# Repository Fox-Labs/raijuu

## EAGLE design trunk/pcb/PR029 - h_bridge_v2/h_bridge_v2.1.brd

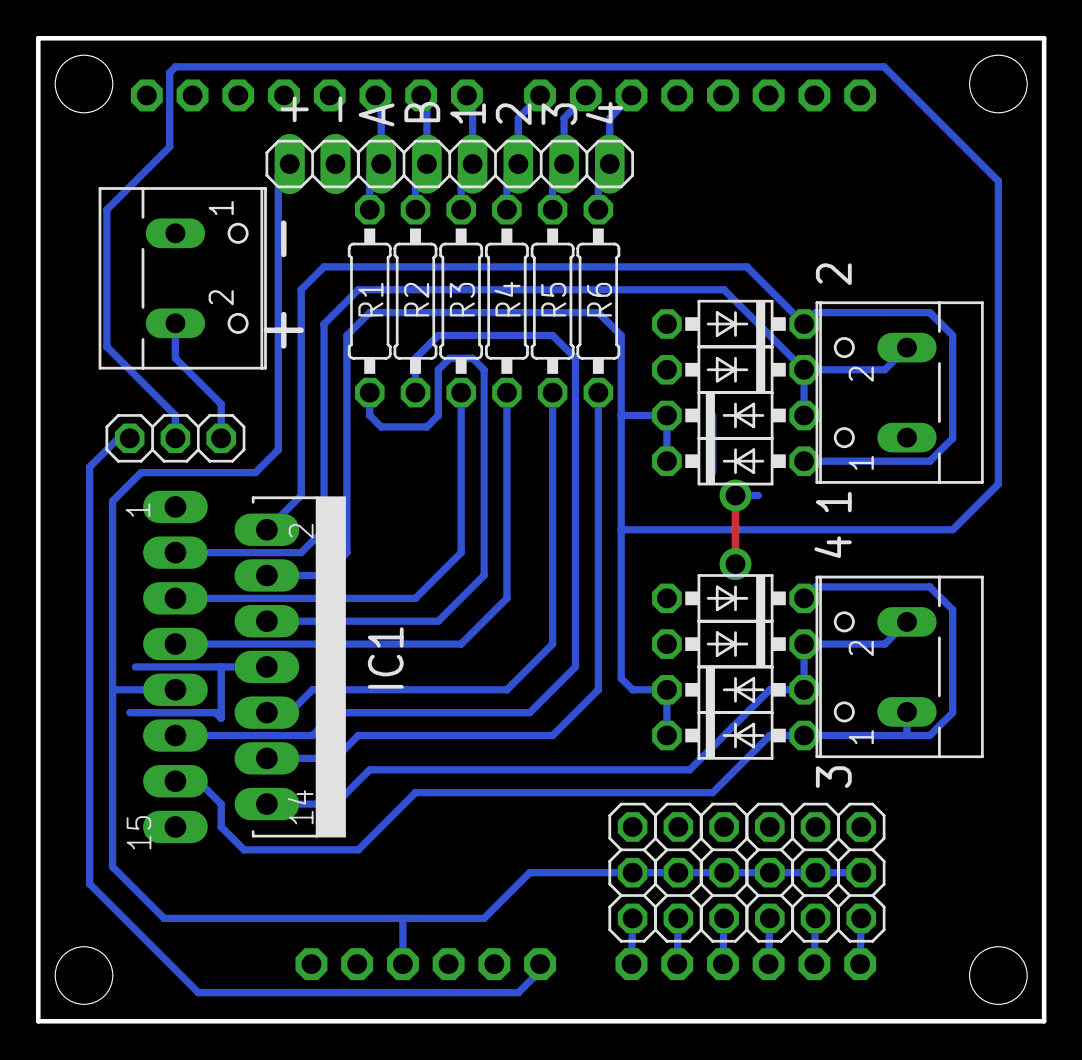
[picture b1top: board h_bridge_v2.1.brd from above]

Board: 2 copper layers, 55.9 x 54.6 mm, 28 parts (0 on the bottom side), 27 nets.

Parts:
D1, D2, D3, D4, D5, D6, D7, D8: 1N4004A; DO41-10
IC1: L298; MULTIWATT-15
JP1: 1X06
JP2, JP3, JP4, JP5, JP6, JP7, JP8: 1X03
JP9: 1X02
R1, R2, R3, R4, R5, R6: 0207/10
U$1: ARDUINO-HOLE
X1, X2, X3: W237-102

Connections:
+5V: IC1.9, JP3.2, JP4.2, JP5.2, JP6.2, JP7.2, JP8.2, JP9.1, U$1.5V
+12V: D1.C, D2.C, D5.C, D6.C, IC1.4, JP2.2
GND: D3.A, D4.A, D7.A, D8.A, IC1.1, IC1.8, IC1.15, JP3.3, JP4.3, JP5.3, JP6.3, JP7.3, JP8.3, JP9.2, U$1.GND, U$1.GND1, U$1.GND2, X3.1
IN_A1: JP1.3, R3.1, U$1.D8
IN_A2: JP1.4, R4.1, U$1.D7
IN_B1: JP1.5, R5.1, U$1.D6
IN_B2: JP1.6, R6.1, U$1.D5
unnamed: IC1.6, R1.2
unnamed: IC1.11, R2.2
unnamed: IC1.5, R3.2
unnamed: IC1.7, R4.2
unnamed: IC1.10, R5.2
unnamed: IC1.12, R6.2
unnamed: JP3.1, U$1.A0
unnamed: JP4.1, U$1.A1
unnamed: JP5.1, U$1.A2
unnamed: JP6.1, U$1.A3
unnamed: JP7.1, U$1.A4
unnamed: JP8.1, U$1.A5
OUT1: D2.A, D4.C, IC1.2, X1.1
OUT2: D1.A, D3.C, IC1.3, X1.2
OUT3: D6.A, D8.C, IC1.13, X2.1
OUT4: D5.A, D7.C, IC1.14, X2.2
PWM_A: JP1.1, R1.1, U$1.D10
PWM_B: JP1.2, R2.1, U$1.D9
PWR: JP2.3, X3.2
VIN: JP2.1, U$1.VIN

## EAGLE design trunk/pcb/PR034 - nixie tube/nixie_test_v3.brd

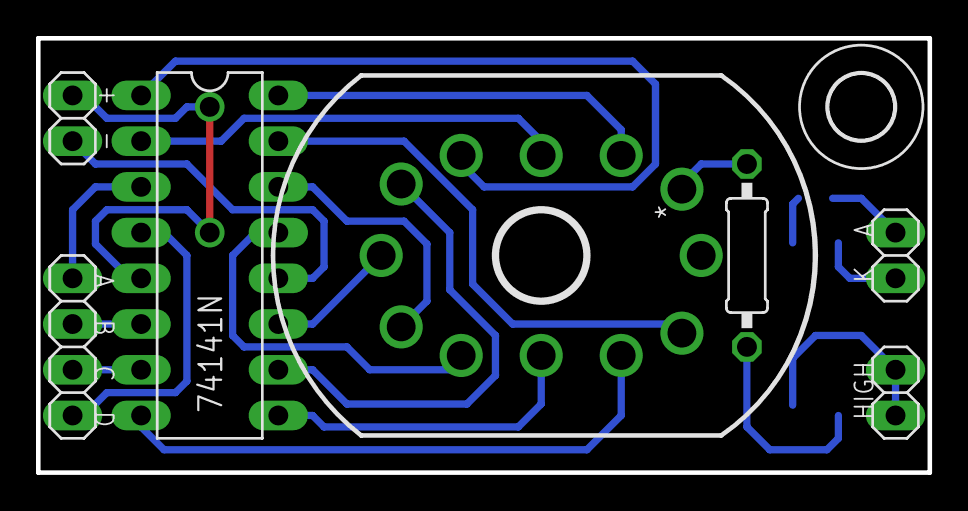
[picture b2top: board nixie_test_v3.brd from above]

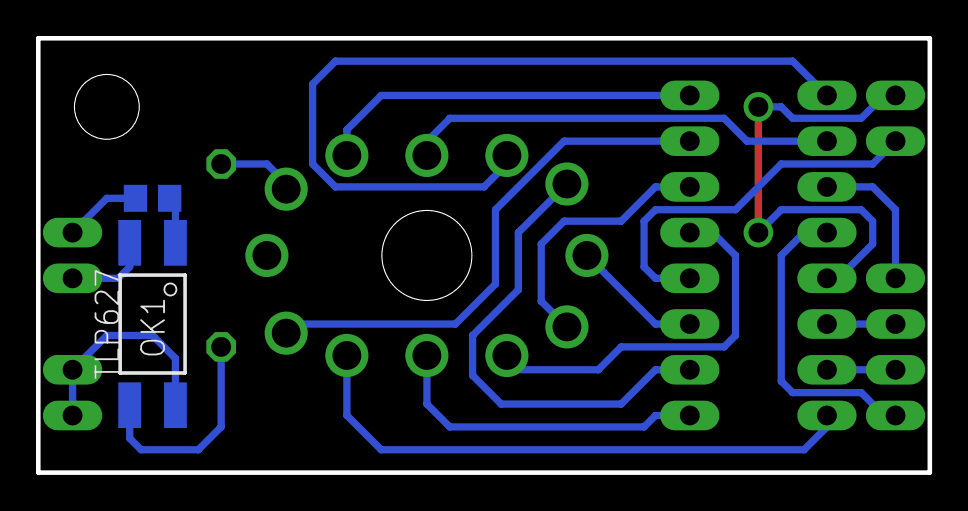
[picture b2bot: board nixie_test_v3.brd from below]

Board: 2 copper layers, 49.5 x 24.1 mm, 10 parts (2 on the bottom side), 22 nets.

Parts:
IC1: 74141N; DIL16
JP1: 1X04
JP2, JP3, JP4: 1X02
N1: IN-12B; IN-12
OK1: TLP627; 4-SMD
R1: 1k; R0805
R2: 22k; 0207/10
U$1: 3,6

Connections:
+5V: IC1.5, JP4.1
+180V: JP3.1, JP3.2, OK1.4
A: IC1.3, JP1.1
B: IC1.6, JP1.2
C: IC1.7, JP1.3
C0: IC1.16, N1.0
C1: IC1.15, N1.1
C2: IC1.8, N1.2
C3: IC1.9, N1.3
C4: IC1.13, N1.4
C5: IC1.14, N1.5
C6: IC1.11, N1.6
C7: IC1.10, N1.7
C8: IC1.1, N1.8
C9: IC1.2, N1.9
D: IC1.4, JP1.4
GND: IC1.12, JP4.2
LA: JP2.1, R1.1
LK: JP2.2, OK1.2
unnamed: N1.A, R2.1
unnamed: OK1.3, R2.2
unnamed: OK1.1, R1.2

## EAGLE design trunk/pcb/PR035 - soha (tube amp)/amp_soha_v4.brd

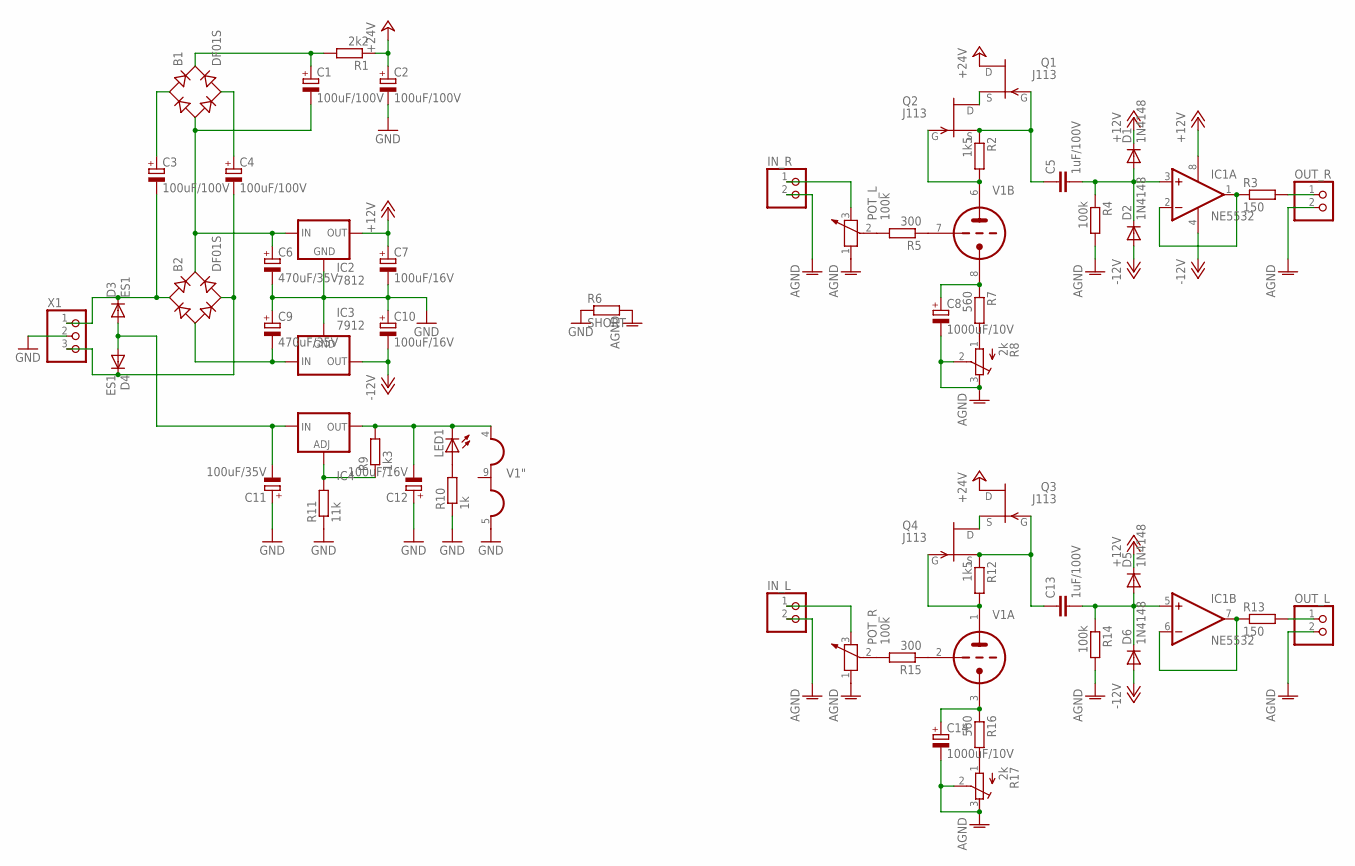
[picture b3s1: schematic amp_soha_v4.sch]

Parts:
B1, B2: DF01S; DFS
C1, C2, C3, C4: 100uF/100V; E5-10,5
C5, C13: 1uF/100V; C075-052X106
C6, C9: 470uF/35V; E5-10,5
C7, C10, C12: 100uF/16V; E2,5-6
C8, C14: 1000uF/10V; E5-10,5
C11: 100uF/35V; E2,5-6
D1, D2, D5, D6: 1N4148; D0805
D3, D4: ES1; DO-214AC
IC1: NE5532; SO08
IC2: 7812; 78XXS
IC3: 7912; 79XXS
IC4: LM337TS; 337TS
IN_L: PINHD-1X2; 1X02
IN_R: PINHD-1X2; 1X02
LED1: LED5MM
OUT_L: PINHD-1X2; 1X02
OUT_R: PINHD-1X2; 1X02
POT_L: 100k; 1X03
POT_R: 100k; 1X03
Q1, Q2, Q3, Q4: J113; TO92
R1: 2k2; R0805
R2, R12: 1k5; R0805
R3, R13: 150; R0805
R4, R14: 100k; R0805
R5, R15: 300; R0805
R6: SHORT
R7, R16: 560; R0805
R8, R17: 2k; RTRIM3296W
R9: 1k3; R0805
R10: 1k; R0805
R11: 11k; R0805
V1: 12AU7-P; NOVAL
X1: W237-103

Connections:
+12V: C7.+, D1.K (C), D5.K (C), IC1.8 (V+), IC2.OUT
+24V: C2.+, Q1.3 (D), Q3.3 (D), R1.1
-12.6V: C12.-, IC4.3 (OUT), LED1.K (C), R9.2, V1.4 (H1)
-12V: C10.-, D2.A, D6.A, IC1.4 (V-), IC3.OUT
AGND: C8.-, C14.-, IN_L.2, IN_R.2, OUT_L.2, OUT_R.2, POT_L.1, POT_R.1, R4.2, R6.2, R8.2 (S), R8.3 (E), R14.2, R17.2 (S), R17.3 (E)
GND: C2.-, C6.-, C7.-, C9.+, C10.+, C11.+, C12.+, IC2.GND, IC3.GND, R6.1, R10.1, R11.1, V1.5 (H3), X1.2
unnamed: B2.AC1, C3.-, D3.C, X1.1
unnamed: B2.AC2, C4.-, D4.C, X1.3
unnamed: C11.-, D3.A, D4.A, IC4.2 (IN)
unnamed: IC4.1 (ADJ), R9.1, R11.2
unnamed: B2.-, C9.-, IC3.IN
unnamed: B1.-, B2.+, C1.-, C6.+, IC2.IN
unnamed: LED1.A, R10.2
unnamed: B1.AC1, C3.+
unnamed: B1.AC2, C4.+
unnamed: R15.1, V1.2 (TG)
unnamed: B1.+, C1.+, R1.2
unnamed: IN_R.1, POT_L.3 (2)
unnamed: POT_L.2 (3), R5.2
unnamed: R5.1, V1.7 (TG)
unnamed: C8.+, R7.1, V1.8 (TK)
unnamed: C5.1, Q1.1 (G), Q2.2 (S), R2.1
unnamed: R7.2, R8.1 (A)
unnamed: R16.2, R17.1 (A)
unnamed: Q2.1 (G), R2.2, V1.6 (TA)
unnamed: Q1.2 (S), Q2.3 (D)
unnamed: Q4.1 (G), R12.2, V1.1 (TA)
unnamed: C5.2, D1.A, D2.K (C), IC1.3 (+IN), R4.1
unnamed: IC1.1 (OUT), IC1.2 (-IN), R3.1
unnamed: OUT_R.1, R3.2
unnamed: IN_L.1, POT_R.3 (2)
unnamed: POT_R.2 (3), R15.2
unnamed: C14.+, R16.1, V1.3 (TK)
unnamed: C13.1, Q3.1 (G), Q4.2 (S), R12.1
unnamed: Q3.2 (S), Q4.3 (D)
unnamed: C13.2, D5.A, D6.K (C), IC1.5 (+IN), R14.1
unnamed: IC1.6 (-IN), IC1.7 (OUT), R13.1
unnamed: OUT_L.1, R13.2

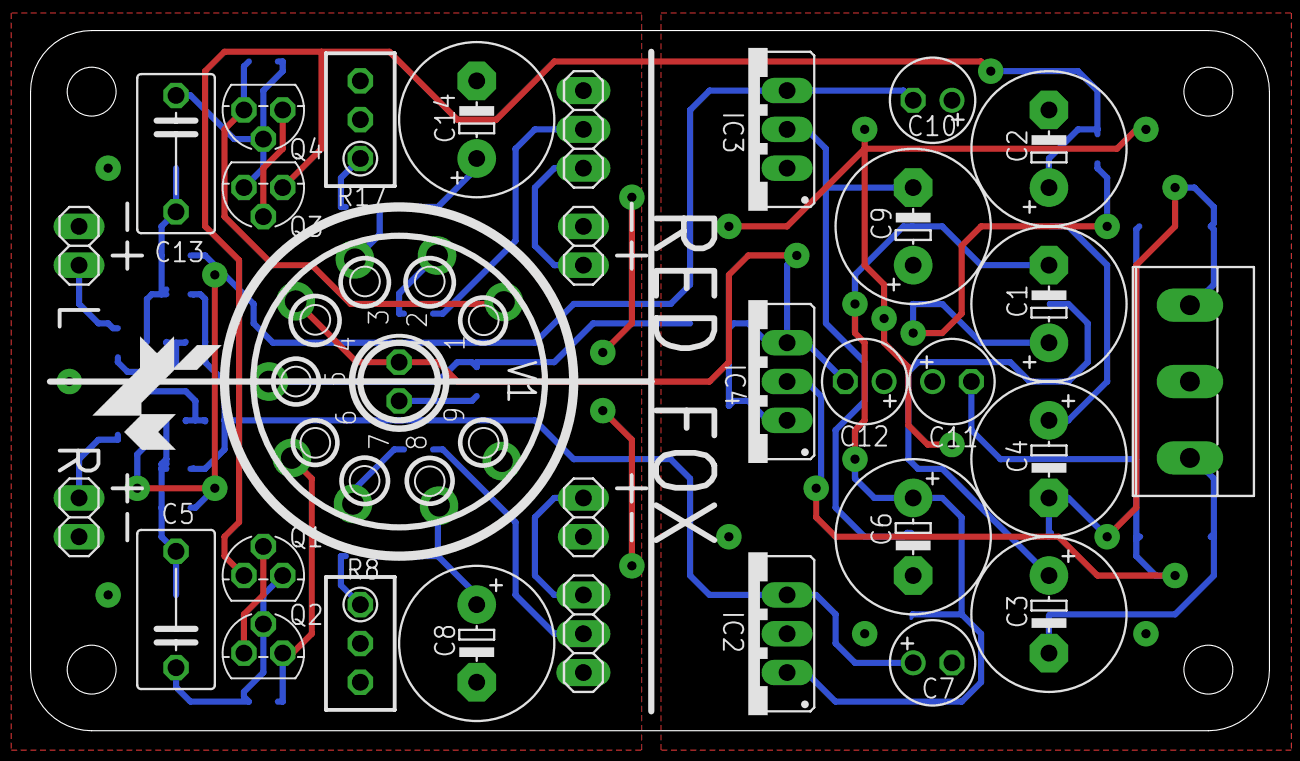
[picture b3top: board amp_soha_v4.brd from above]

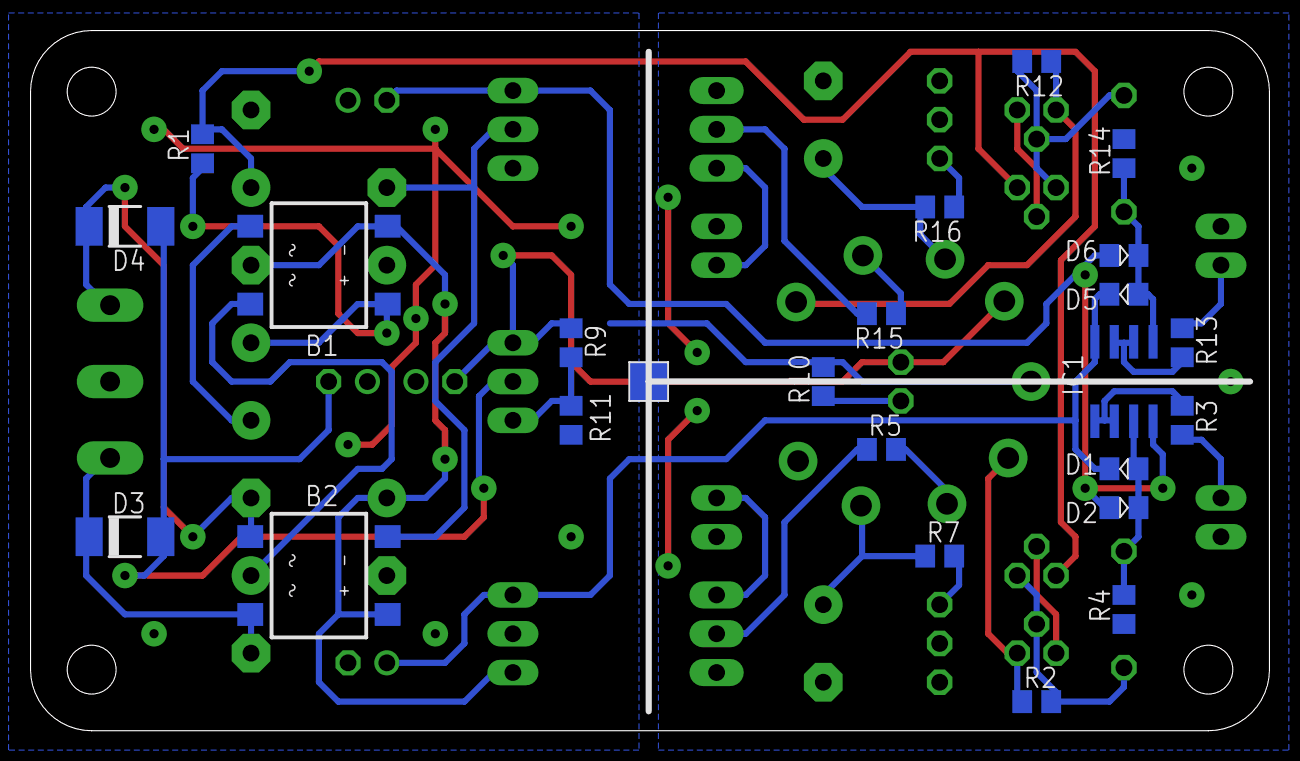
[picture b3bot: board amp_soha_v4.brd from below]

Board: 2 copper layers, 81.1 x 45.8 mm, 57 parts (24 on the bottom side), 38 nets.

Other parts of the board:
U$1: FOX-2

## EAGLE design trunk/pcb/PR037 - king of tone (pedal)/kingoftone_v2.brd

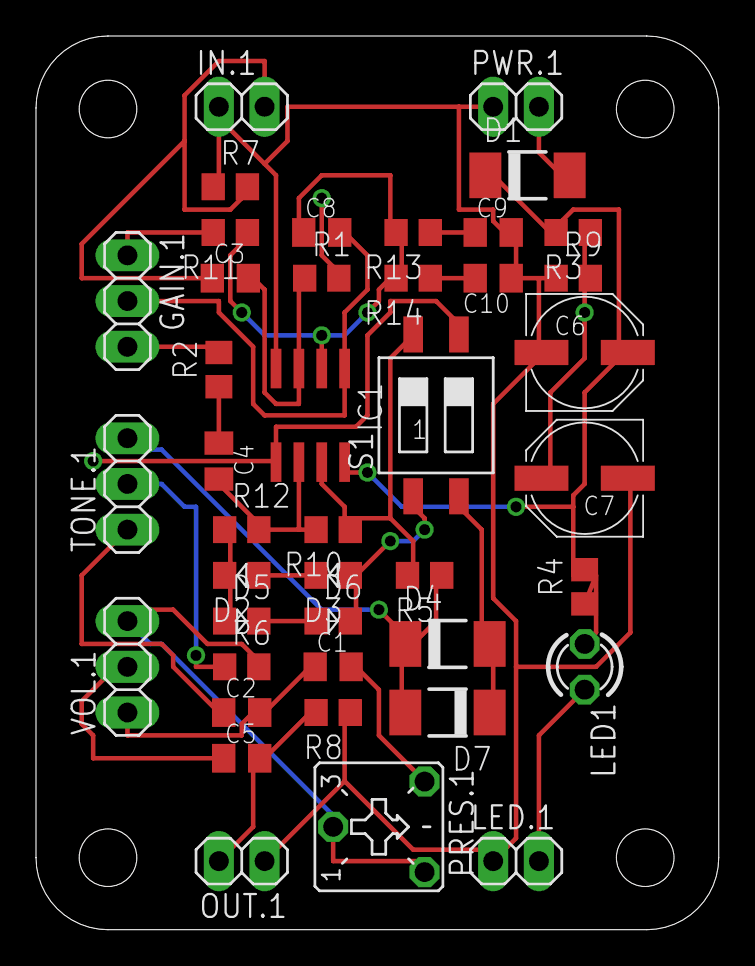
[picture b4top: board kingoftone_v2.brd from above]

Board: 2 copper layers, 37.9 x 49.6 mm, 42 parts (0 on the bottom side), 29 nets.

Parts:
C1, C2, C3, C9, C10: 10nF; C0805K
C4: 100nF; C0805K
C5: 1uF; C0805K
C6, C7: 100uF; PANASONIC_D
C8: 100pF; C0805K
D1: ES1; DO-214AC
D2, D3, D5, D6: 1N4148; D0805
D4, D7: S1M; DO-214AC
GAIN.1: 100kB; 1X03
IC1: NE5535U; SO08
IN.1: 1X02
LED1: LED3MM
LED.1: 1X02
OUT.1: 1X02
PRES.1: 50k; CT6
PWR.1: 1X02
R1, R7, R8: 1M; R0805
R2, R11: 10k; R0805
R3, R9: 47k; R0805
R4, R5: 1k; R0805
R6, R12: 6k8; R0805
R10: 220k; R0805
R13: 27k; R0805
R14: 33k; R0805
S1: SWS002; SMS-002
TONE.1: 25kB; 1X03
VOL.1: 100kA; 1X03

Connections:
+4.5V: C1.1, C2.2, C7.+, IC1.5, R1.2, R3.1, R9.2, S1.3, VOL.1.1
+9V: C6.+, D1.C, IC1.8, R3.2, R4.2
GND: C6.-, C7.-, C9.2, C10.1, IC1.4, IN.1.1, LED.1.1, OUT.1.1, PWR.1.1, R7.1, R8.1, R9.1
unnamed: C3.1, IN.1.2, R7.2
unnamed: C3.2, IC1.3, R1.1
unnamed: C8.1, IC1.2, R11.1, R13.2, R14.2
unnamed: C8.2, GAIN.1.2, IC1.1
unnamed: C9.1, R13.1
unnamed: C10.2, R14.1
unnamed: GAIN.1.1, R11.2
unnamed: C4.1, R2.1
unnamed: GAIN.1.3, R2.2
unnamed: C4.2, IC1.6, R10.2, R12.2
unnamed: IC1.7, R5.2, R10.1, S1.4
unnamed: D2.A, D3.K
unnamed: D2.K, D5.A, R12.1
unnamed: D5.K, D6.A
unnamed: D3.A, D6.K, S1.1
unnamed: D4.C, D7.A, R5.1, TONE.1.3
unnamed: D4.A, D7.C, S1.2
unnamed: C5.1, VOL.1.2
unnamed: R6.1, TONE.1.2
unnamed: C2.1, TONE.1.1
unnamed: C1.2, PRES.1.E
unnamed: PRES.1.A, PRES.1.S, R6.2, VOL.1.3
unnamed: C5.2, OUT.1.2, R8.2
unnamed: D1.A, PWR.1.2
unnamed: LED1.A, R4.1
unnamed: LED1.K, LED.1.2

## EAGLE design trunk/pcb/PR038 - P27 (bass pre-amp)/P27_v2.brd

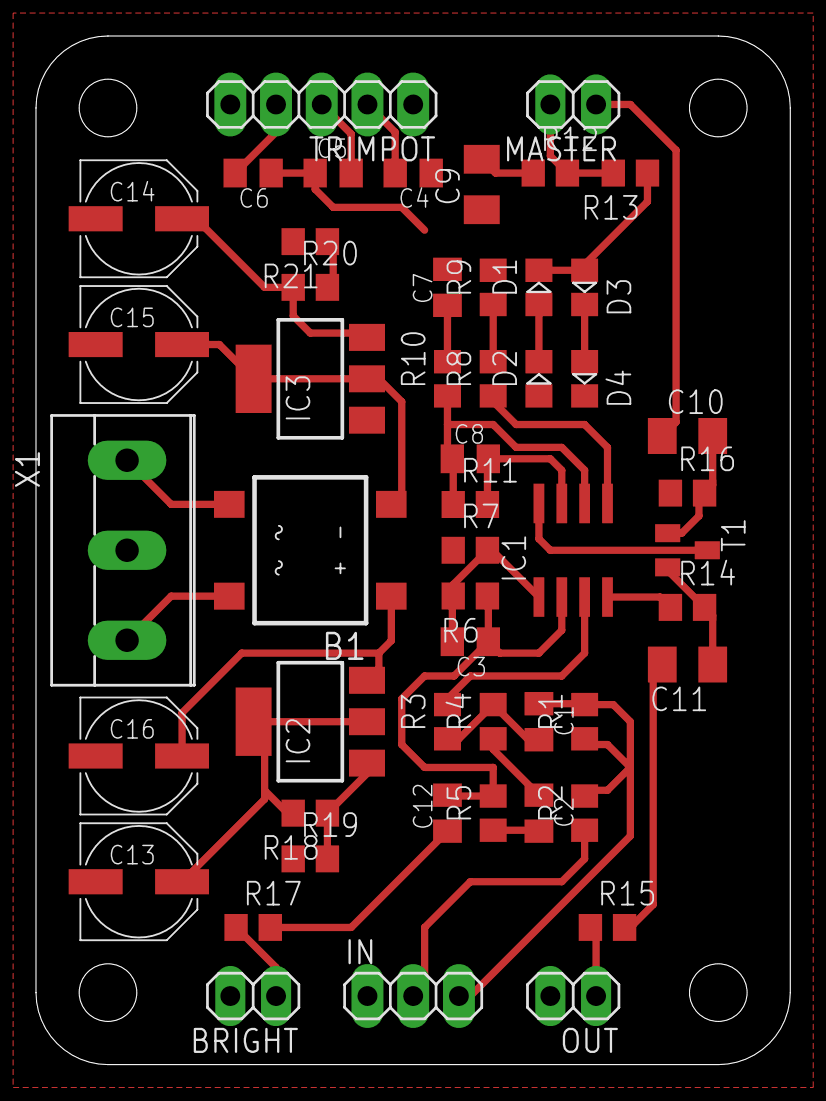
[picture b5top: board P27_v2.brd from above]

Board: 2 copper layers, 41.9 x 57.1 mm, 52 parts (0 on the bottom side), 38 nets.

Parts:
B1: DF01S; DFS
BRIGHT: 1X02
C1: 47nF; C0805K
C2, C7: 1uF; C0805K
C3, C8: 120pF; C0805K
C4: 1nF; C0805K
C5: 220nF; C0805K
C6: 100nF; C0805K
C9, C10: 2.2uF; C1206
C11: 10uF; C1206
C12: 22nF; C0805K
C13, C14, C15, C16: PANASONIC_D
D1, D2, D3, D4: 1N4148; D0805
IC1: NE5532U; SO08
IC2: LM317; SOT223
IC3: LM337; SOT223
IN: 1X03
MASTER: 1X02
OUT: 1X02
R1: 22k; R0805
R2, R16: 100k; R0805
R3, R8, R14: 2k2; R0805
R4, R9: 1M; R0805
R5, R10, R12: 4k7; R0805
R6, R11: 68k; R0805
R7: 33k; R0805
R13: 220; R0805
R15: 100; R0805
R17: 1k; R0805
R18, R20: 2k; R0805
R19, R21: 240; R0805
T1: BC549; SOT23
TRIMPOT: 1X05
X1: W237-103

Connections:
+12V: C13.+, IC1.8, IC2.2, IC2.4, R18.2, T1.3
-12V: C14.+, IC1.4, IC3.3, R14.1, R20.1
AGND: BRIGHT.2, C2.1, C7.2, C13.-, C14.-, C15.-, C16.-, D2.A, D4.K, IN.1, OUT.2, R4.1, R9.2, R16.1, R19.1, R21.2, TRIMPOT.5, X1.2
unnamed: C1.1, R1.2, R2.2
unnamed: IC1.3, R3.2
unnamed: C1.2, R3.1, R4.2
unnamed: C3.1, C12.2, IC1.2, R5.2, R6.1
unnamed: C2.2, R5.1
unnamed: C3.2, C4.1, IC1.1, R6.2, R7.2
unnamed: C6.2, TRIMPOT.4
unnamed: C5.1, C6.1, R7.1
unnamed: C5.2, TRIMPOT.3
unnamed: C4.2, TRIMPOT.2
unnamed: C10.2, R16.2, T1.1
unnamed: C7.1, R10.2
unnamed: R8.2, R9.1, TRIMPOT.1
unnamed: IC1.5, R8.1
unnamed: C11.1, R14.2, T1.2
unnamed: C11.2, R15.2
unnamed: C8.1, IC1.6, R10.1, R11.1
unnamed: C8.2, C9.1, IC1.7, R11.2
unnamed: OUT.1, R15.1
unnamed: C9.2, R12.1
unnamed: MASTER.2, R12.2, R13.2
unnamed: D1.A, D2.K
unnamed: D3.K, D4.A
unnamed: D1.K, D3.A, R13.1
unnamed: IN.3, R1.1
unnamed: IN.2, R2.1
unnamed: C10.1, MASTER.1
unnamed: B1.AC1, X1.3
unnamed: C12.1, R17.2
unnamed: BRIGHT.1, R17.1
unnamed: B1.AC2, X1.1
unnamed: B1.+, C16.+, IC2.3
unnamed: B1.-, C15.+, IC3.2, IC3.4
unnamed: IC2.1, R18.1, R19.2
unnamed: IC3.1, R20.2, R21.1

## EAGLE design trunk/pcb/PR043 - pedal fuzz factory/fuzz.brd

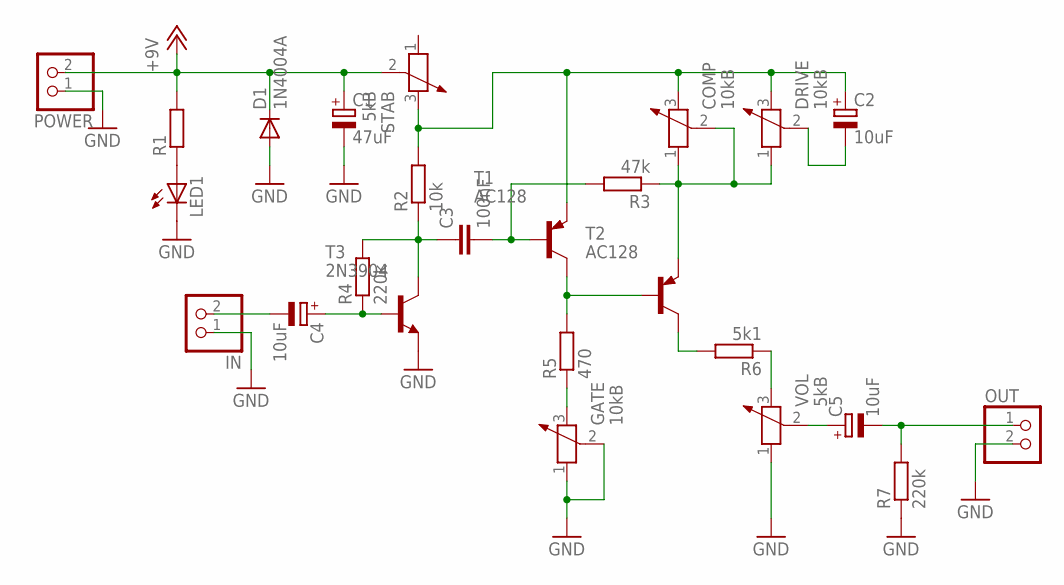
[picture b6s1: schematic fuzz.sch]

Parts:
C1: 47uF; E2,5-6
C2, C4, C5: 10uF; E2,5-6
C3: 100nF; C050-045X075
COMP: 10kB; 1X03
D1: 1N4004A; DO41-5
DRIVE: 10kB; 1X03
GATE: 10kB; 1X03
IN: PINHD-1X2; 1X02
LED1: LED3MM
OUT: PINHD-1X2; 1X02
POWER: PINHD-1X2; 1X02
R1: R-EU_; R0805
R2: 10k; 0207/7
R3: 47k; 0207/7
R4, R7: 220k; 0207/7
R5: 470; 0207/7
R6: 5k1; 0207/7
STAB: 5kB; 1X03
T1, T2: AC128; TO18
T3: 2N3904; TO92
VOL: 5kB; 1X03

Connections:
+12V: C1.+, D1.C, POWER.2, R1.2, STAB.2 (3)
GND: C1.-, D1.A, GATE.1, GATE.2 (3), IN.1, LED1.K (C), OUT.2, POWER.1, R7.1, T3.3 (E), VOL.1
unnamed: LED1.A, R1.1
unnamed: C4.+, R4.1, T3.2 (B)
unnamed: C2.+, COMP.3 (2), DRIVE.3 (2), R2.2, STAB.3 (2), T1.1 (E)
unnamed: C3.1, R2.1, R4.2, T3.1 (C)
unnamed: C3.2, R3.2, T1.2 (B)
unnamed: C2.-, DRIVE.2 (3)
unnamed: COMP.1, COMP.2 (3), DRIVE.1, R3.1, T2.1 (E)
unnamed: R5.2, T1.3 (C), T2.2 (B)
unnamed: GATE.3 (2), R5.1
unnamed: R6.2, T2.3 (C)
unnamed: R6.1, VOL.3 (2)
unnamed: C5.+, VOL.2 (3)
unnamed: C5.-, OUT.1, R7.2
unnamed: C4.-, IN.2

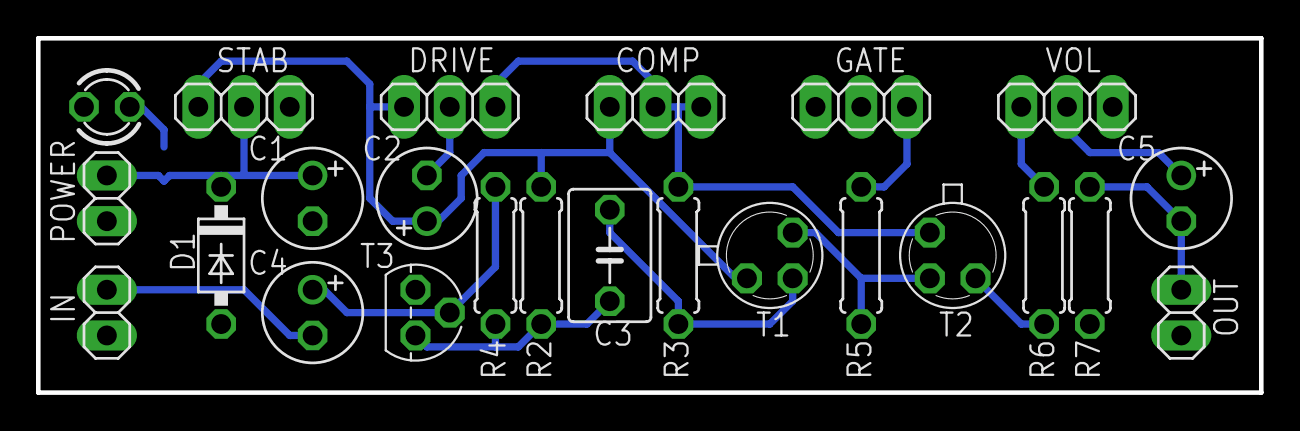
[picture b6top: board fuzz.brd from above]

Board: 2 copper layers, 67.9 x 19.7 mm, 25 parts (1 on the bottom side), 16 nets.
